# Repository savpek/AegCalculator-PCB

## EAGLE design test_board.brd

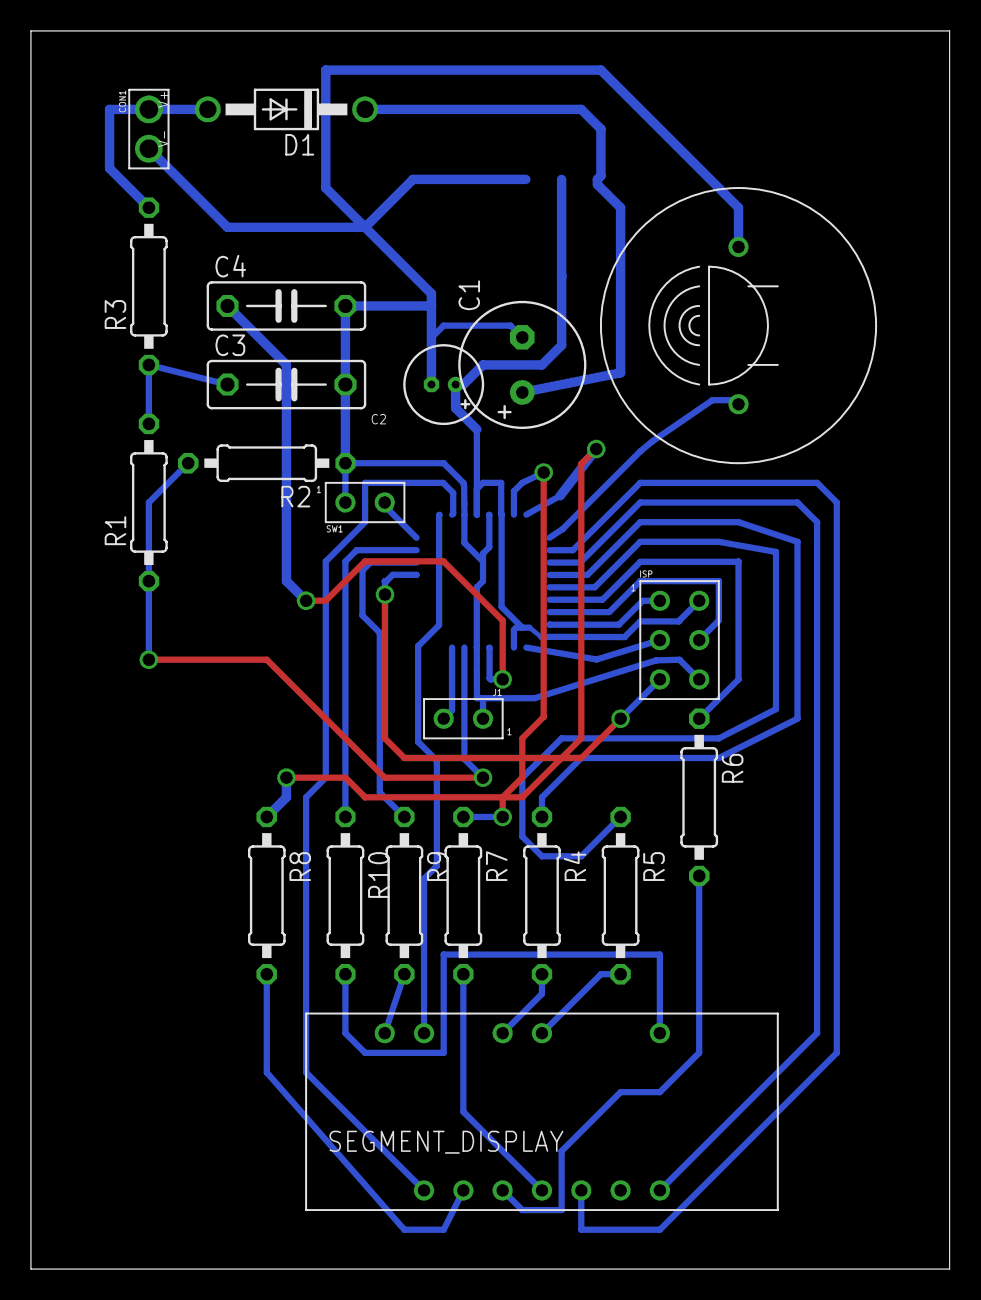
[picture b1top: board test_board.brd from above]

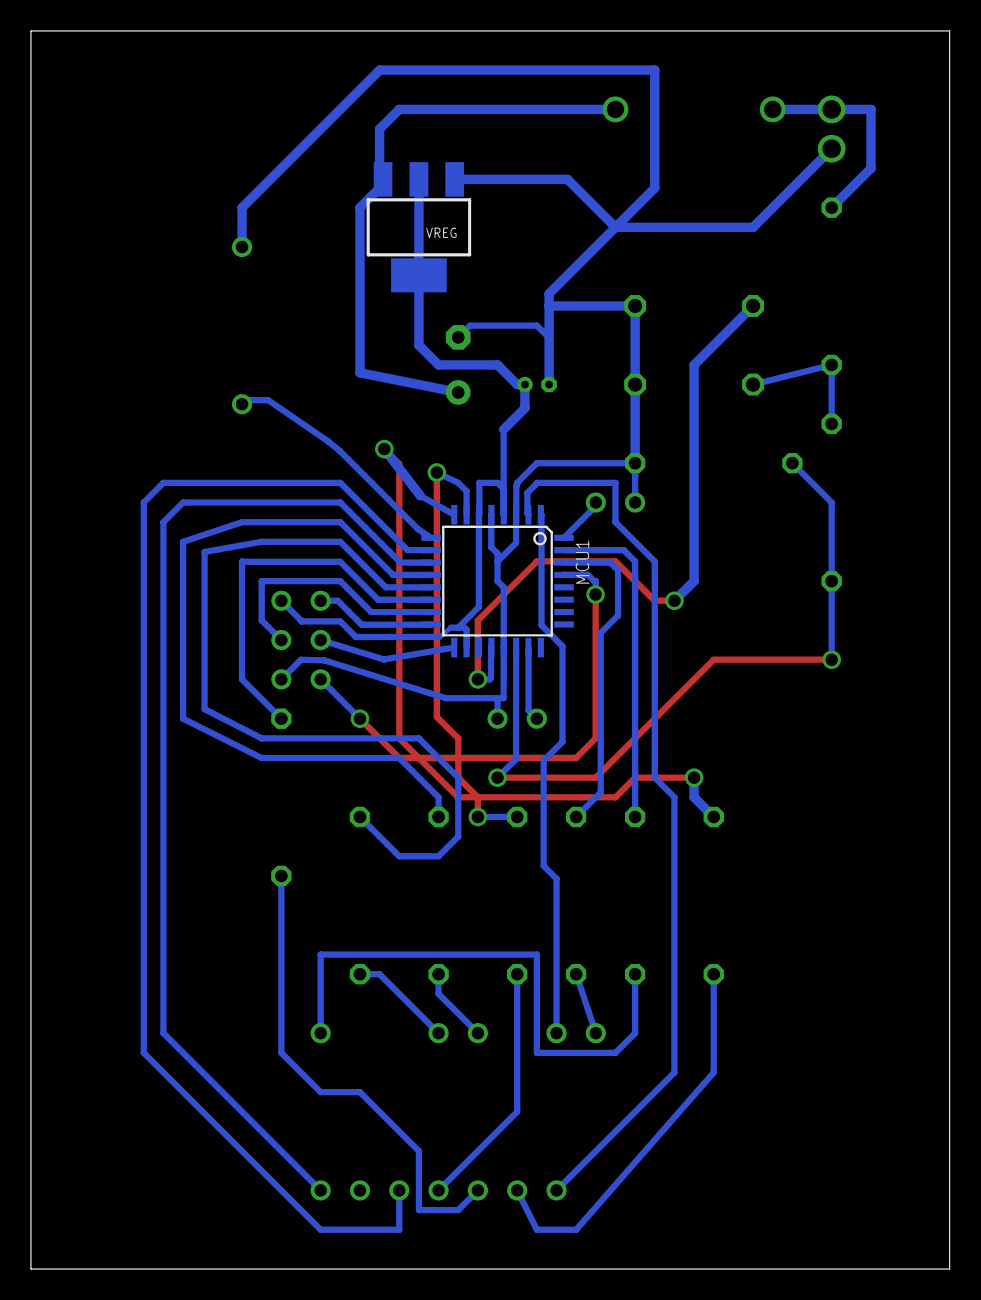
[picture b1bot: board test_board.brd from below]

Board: 2 copper layers, 59.4 x 80.0 mm, 23 parts (2 on the bottom side), 32 nets.

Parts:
BZ1: PS1720P02_BUZZER
C1: 220uF; E3,5-8
C2: 22uF; E1.5-5
C3, C4: 100nF; C075-032X103
CON1: CONNECTOR_2PIN1X2_POWER_WIRE; 1X2_POWER_WIRE
D1: 1N4004; DO41-10
ISP: CONNECTOR_6PIN2X3_ISP; 2X3_ISP
J1: CONNECTOR_2PIN1X2; 1X2_GENERIC
MCU1: ATMEGA48-20PU-32TQFP; TQFP32-08-HOMEETCH
R1: 1M; 0207/10
R2: 500k; 0207/10
R3, R4, R5, R6, R7, R8, R9, R10: 1k; 0207/10
SEGMENT1: SEGMENT_CLOCK_MODULE_3_DIGIT_COMMON_CATHODE; SEGMENT_CLOCK_DISPLAY_HDSP_433G
SW1: CONNECTOR_2PIN1X2; 1X2_GENERIC
VREG: 5VREG_TLV1117; SOT223

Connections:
#RESET: ISP.RST, MCU1.29
+5V: C2.+, ISP.V+, MCU1.4, MCU1.6, MCU1.18, VREG.2, VREG.4
GND: BZ1.P$2, C1.-, C2.-, C3.2, C4.2, CON1.V-, ISP.GND, J1.1, MCU1.3, MCU1.5, MCU1.21, R2.1, SW1.1, VREG.1
MISO: ISP.MISO, MCU1.16
MOSI: ISP.MOSI, MCU1.15
unnamed: C1.+, D1.C, VREG.3
unnamed: C4.1, MCU1.20
unnamed: J1.2, MCU1.23
unnamed: MCU1.22, R1.1, R2.2
unnamed: C3.1, R1.2, R3.1
unnamed: R4.2, SEGMENT1.10
unnamed: R5.2, SEGMENT1.9
unnamed: R6.2, SEGMENT1.3
unnamed: R7.2, SEGMENT1.4
unnamed: R8.2, SEGMENT1.2
unnamed: R9.2, SEGMENT1.12
unnamed: R10.2, SEGMENT1.8
unnamed: BZ1.P$1, MCU1.9
PB0: MCU1.12, R4.1
PB1: MCU1.13, R5.1
PB2: MCU1.14, R6.1
PB6: MCU1.7, R7.1
PB7: MCU1.8, R8.1
PD0: MCU1.30, R9.1
PD1: MCU1.31, R10.1
PD2(INT0): MCU1.32, SW1.2
PD3: MCU1.1, SEGMENT1.11
PD4: MCU1.2, SEGMENT1.1
PD6: MCU1.10, SEGMENT1.5
PD7: MCU1.11, SEGMENT1.7
SCK: ISP.SCK, MCU1.17
V_GUNBATTERY: CON1.V+, D1.A, R3.2

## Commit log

2012-07-25 Initial commit.
